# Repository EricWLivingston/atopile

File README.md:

<h1 align="center">
    <picture>
    <source media="(prefers-color-scheme: dark)" srcset="https://github.com/atopile/atopile/assets/9785003/00f19584-18a2-4b5f-9ce4-1248798974dd">
    <source media="(prefers-color-scheme: light)" src="https://github.com/atopile/atopile/assets/9785003/d38941c1-d7c1-42e6-9b94-a62a0996bc19">
    
    </picture>
</h1>

<p align="center">
  <b>EE Agent fork of atopile</b> — an AI electrical-engineering design agent built on top of the atopile compiler.
</p>

<p align="center">
  <a href="https://github.com/atopile/atopile">Upstream atopile</a> ·
  <a href="https://docs.atopile.io/">atopile docs</a> ·
  <a href="LICENSE">MIT License</a>
</p>

---

> **This is a fork.** It tracks [atopile/atopile](https://github.com/atopile/atopile) and adds
> an EE design agent plus the infrastructure it needs (a dual-provider LLM runner, three custom
> design tools, a KiCad schematic emitter, human-readable net naming, and parametric diode
> picking). For the base language, compiler, and toolchain, see the
> [upstream README](https://github.com/atopile/atopile/blob/main/README.md) and
> [docs.atopile.io](https://docs.atopile.io/). Everything below is **what this fork adds.**

## What this fork adds

atopile lets you describe electronics as code (`.ato`) and compiles them to a BOM, netlist, and
KiCad layout. This fork wraps an **agent** around that compiler: it researches a design against an
indexed knowledge base, authors `.ato`, simulates analog subcircuits, drives the build, and emits a
human-readable KiCad schematic — switchable between OpenAI and Anthropic models, with per-turn
model routing for cost control. The agent runs in the existing atopile VS Code extension sidebar.

This is an **early prototype**: the core agent loop, the three tools, and the schematic/net-naming
pipeline are working and tested, but several pieces are stubs or single-vendor (see
[Known limitations](#known-limitations--status)).

## Features

### Dual-provider agent runner — `src/atopile/server/agent/_ee/`
- **`AnthropicProvider`** (`provider_anthropic.py`) implements atopile's `LLMProvider` protocol
  alongside the existing OpenAI provider. It emulates the OpenAI stateful Responses API on top of
  Anthropic's stateless Messages API via an LRU transcript store, and repairs orphaned
  `tool_use`/`tool_result` pairs (the failure class that froze multi-turn runs).
- **Dynamic model routing** (`model_router.py`) — a per-turn complexity classifier routes calls to
  Haiku / Sonnet / Opus tiers, with a content-based floor and mid-turn escalation on repeated build
  failures. Off by default; opt-in, Anthropic-only.
- **Runner safeguards** — per-turn token budget, build-failure detection (the async build queue
  otherwise hides failures from the circuit breaker), and tightened loop/time caps.

### Custom agent tools — `_ee/tools_*.py` + framework-agnostic packages
- **`rag_search`** — retrieval over a datasheet/app-note corpus: `src/ee_agent_rag/`
  (Chroma · LlamaParse-REST · OpenAI embeddings · Cohere rerank, RRF fusion). Tuned to recall@5 ≈
  0.98 on a 50-question eval; thin wrapper degrades to `{ok: false}` on any failure.
- **`pyspice_run`** — simulates an agent-authored SPICE netlist: `src/ee_agent_spice/`
  (PySpice + libngspice, bundled discrete models). Returns per-probe min/max/mean only;
  persists full vectors to disk.
- **`skills_list` / `skill_read`** (`tools_skills.py`) — on-demand skill discovery so the agent
  pulls per-tool guidance just-in-time instead of always-loading it.
- **`ipc_check`** — registered, schema'd graceful **stub** (body TBD).

### KiCad schematic emitter — `src/faebryk/exporters/schematic/`
atopile had no Python `.kicad_sch` writer; this adds one (emitting S-expression text directly,
because `kicad.dumps` mis-writes schematics). Build step `generate_schematic` writes
`<output>.kicad_sch`. Modes (`export_schematic(mode=…)`): **hierarchical** (default — one sheet per
`.ato` module, global labels = a valid netlist), **wired** (provably short-free ladder routing), and
**labels**. Real cached symbols are regenerated into the schematic's native grammar; rails render as
KiCad power symbols. Sheet grouping is refined by connectivity (`schematic.py`:
`_pull_in_by_connectivity`, `_flatten_small_leaves`) so parent-level passives land on the subcircuit
they belong to.

### Human-readable net naming — `src/faebryk/libs/net_naming.py`
Voltage-aware power rails (`+5V` / `+3V3` / `+12V`, from the tightest-spec member), a single shared
`GND` with a fragmentation warning, and an IC-pin fallback for unnamed nets — so the emitted
schematic labels read like a human drew them.

### Parametric diode auto-picking — `src/faebryk/library/Diode.py`, `Pickable.py`
Adds the `DIODES` query endpoint + `is_pickable_by_type` to `Diode`, fixing the silent "ghost
component" drop where an un-pickable diode vanished from the BOM/netlist/PCB while its nets
remained. (MOSFET/LED auto-pick is scoped but deliberately deferred.)

### Agent run-log viewer — `src/ui-server/`, `src/vscode-atopile/`
A new "Agent" mode in the extension's Logs tab streams the agent's own run log
(`agent_events`), so planning, tool calls, and `run_failed` are visible live.

## Configuration

The provider and agent behaviour are env-driven (read once at process start — **restart the backend
/ reload the VS Code window after changing them**):

| Variable | Purpose |
|---|---|
| `EE_AGENT_PROVIDER` | `openai` (default, upstream behaviour) or `anthropic` |
| `ATOPILE_AGENT_ANTHROPIC_API_KEY` / `ANTHROPIC_API_KEY` | Anthropic credentials |
| `EE_AGENT_DYNAMIC_MODEL` | `1` enables per-turn model routing (Anthropic only; off by default) |
| `ATOPILE_AGENT_MODEL_COMPLEX` | complex-tier model (default Sonnet; set to `claude-opus-4-8` to opt into Opus) |
| `ATOPILE_AGENT_MAX_TURN_TOKENS` / `ATOPILE_AGENT_MAX_BUILD_FAILURES` | per-turn spend / failure budgets |
| `OPENAI_API_KEY` / `LLAMA_CLOUD_API_KEY` / `COHERE_API_KEY` | `rag_search` ingest + query (see `.env.example`) |
| `EE_DATA_ROOT` | RAG corpus/index root (defaults to the source tree) |
| `EE_SPICE_NGSPICE_LIB` / `EE_SPICE_TIMEOUT_S` | libngspice path override / sim wall-clock timeout |

`rag_search` needs a `brew`/pip RAG stack; `pyspice_run` needs `brew install ngspice` (libngspice 46).

## Testing

Run the suite with `ato dev test` (or `pytest -q`). The fork adds **18 test files / ~195 tests**:

- `test/server/agent/` — Anthropic provider, model router, runner safeguards, tool plumbing
- `test/exporters/` — schematic emitter + connectivity placement
- `test/ee_agent_rag/` — RAG pipeline + table-fidelity
- `test/ee_agent_spice/` — SPICE runner (+ a live, auto-skipped tier)

## Known limitations & status

- **`ipc_check` is a stub** — registered and model-callable, but returns a placeholder; it depends on
  a standards corpus (IPC-2221/2152) not yet ingested.
- **Single-vendor auto-pick** — only diodes auto-pick; MOSFETs/LEDs/other actives remain manual.
- **Silent-ghost UX** — an un-pickable, un-footprinted module still logs only `ATTENTION: …` and the
  build reports success (`src/faebryk/libs/picker/picker.py:165`); diodes are fixed, other types are
  not. Promoting that to a visible warning is a one-line policy change with upstream-visible impact.
- **Schematic real-symbol lookup** misses parts whose cached directory name doesn't match the
  sanitized manufacturer string — they fall back to a (electrically complete) generic box.
- **Dynamic routing is Anthropic-only and per-turn** — because the agent runs a whole design as one
  turn, the per-turn route effectively pins the whole run; the OpenAI path is unverified for mid-chain
  model switches, so routing is forced off there. The per-turn token budget does **not** count cache
  reads.
- **RAG corpus is datasheets + app-notes only** — standards/textbook chunkers are pending.
- **`kicad.dumps` for schematics is broken upstream** — worked around by emitting S-expression text;
  a clean upstream fix is a contribution candidate.

## License

MIT — same as upstream atopile. See `LICENSE`.

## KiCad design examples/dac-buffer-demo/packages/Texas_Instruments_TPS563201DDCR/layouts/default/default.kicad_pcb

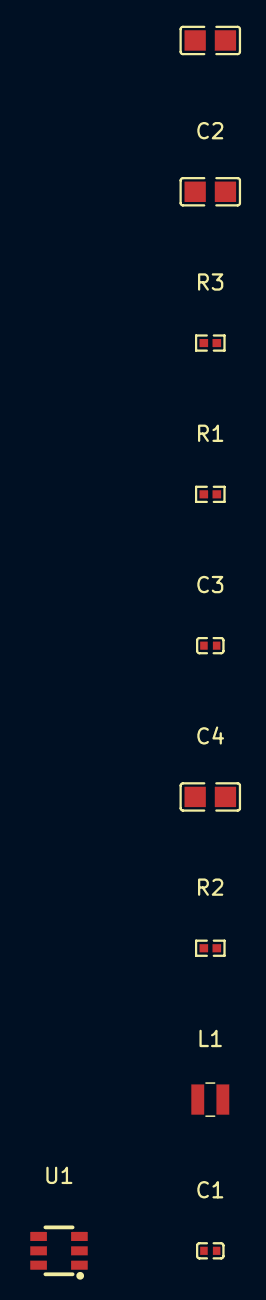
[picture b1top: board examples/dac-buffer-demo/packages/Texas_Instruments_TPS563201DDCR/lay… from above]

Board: 2 copper layers, 10 parts (0 on the bottom side), 7 nets, no tracks yet.

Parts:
C1, C3: 100nF; C0402
C2: 10µF; C0805
C4, C5: 22µF; C0805
L1: L 4.7µH; IND-SMD_L2.5-W2.0-VLS252012CX-150M
R1: 100kΩ; R0402
R2: 10kΩ; R0402
R3: 54.9kΩ; R0402
U1: SOT-23-6_L2.9-W1.6-P0.95-LS2.8-BR

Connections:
EN: R1.1, U1.5
VFB: R2.1, R3.2, U1.4
cin_hf-power-hv: C2.1, C3.1, R1.2, U1.3
cout[1]-power-hv: C4.1, C5.1, L1.2, R3.1
cout[1]-power-lv: C2.2, C3.2, C4.2, C5.2, R2.2, U1.1
hv: C1.1, U1.6
lv: C1.2, L1.1, U1.2

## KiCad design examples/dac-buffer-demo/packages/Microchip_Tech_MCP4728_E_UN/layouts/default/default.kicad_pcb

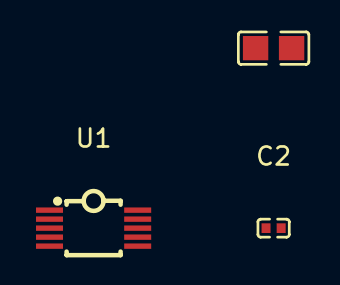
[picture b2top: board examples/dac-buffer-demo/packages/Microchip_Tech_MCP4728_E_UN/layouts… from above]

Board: 2 copper layers, 3 parts (0 on the bottom side), 2 nets, no tracks yet.

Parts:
C1: 10µF; C0805
C2: 100nF; C0402
U1: MSOP-10_L3.0-W3.0-P0.50-LS5.0-TL

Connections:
hv: C1.1, C2.1, U1.1
lv: C1.2, C2.2, U1.10

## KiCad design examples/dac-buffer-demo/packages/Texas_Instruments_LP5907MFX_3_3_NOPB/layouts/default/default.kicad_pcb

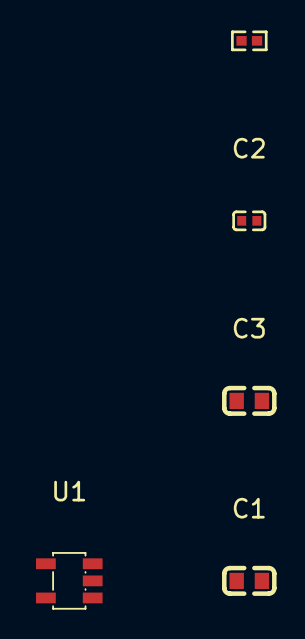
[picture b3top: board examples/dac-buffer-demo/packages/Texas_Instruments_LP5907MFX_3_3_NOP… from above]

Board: 2 copper layers, 5 parts (0 on the bottom side), 4 nets, no tracks yet.

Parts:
C1, C3: 1µF; C0603
C2: 10nF; C0402
R1: 100kΩ; R0402
U1: SOT-23-5_L3.0-W1.7-P0.95-LS2.8-BR

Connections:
cnr-power-hv: C2.1, R1.1, U1.3
cout-power-hv: C3.1, U1.5
hv: C1.1, R1.2, U1.1
lv: C1.2, C2.2, C3.2, U1.2

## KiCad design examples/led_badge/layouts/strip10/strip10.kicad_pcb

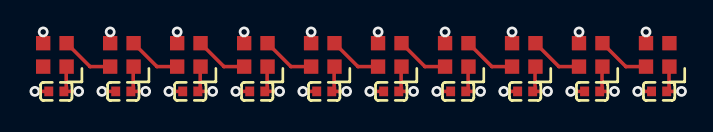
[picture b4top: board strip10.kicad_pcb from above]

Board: 2 copper layers, 20 parts (0 on the bottom side), 11 nets.

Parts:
C1, C2, C3, C4, C5, C6, C7, C8, C9, C10: 100nF; C0402
LED1, LED2, LED3, LED4, LED5, LED6, LED7, LED8, LED9, LED10: LED-SMD_4P-L2.0-W2.0-BR

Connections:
hv: C1.1, C2.1, C3.1, C4.1, C5.1, C6.1, C7.1, C8.1, C9.1, C10.1, LED1.1, LED2.1, LED3.1, LED4.1, LED5.1, LED6.1, LED7.1, LED8.1, LED9.1, LED10.1
leds[1]-data_in-DIN: LED1.2, LED2.4
leds[2]-data_in-DIN: LED2.2, LED3.4
leds[3]-data_in-DIN: LED3.2, LED4.4
leds[4]-data_in-DIN: LED4.2, LED5.4
leds[5]-data_in-DIN: LED5.2, LED6.4
leds[6]-data_in-DIN: LED6.2, LED7.4
leds[7]-data_in-DIN: LED7.2, LED8.4
leds[8]-data_in-DIN: LED8.2, LED9.4
leds[9]-data_in-DIN: LED9.2, LED10.4
lv: C1.2, C2.2, C3.2, C4.2, C5.2, C6.2, C7.2, C8.2, C9.2, C10.2, LED1.3, LED2.3, LED3.3, LED4.3, LED5.3, LED6.3, LED7.3, LED8.3, LED9.3, LED10.3

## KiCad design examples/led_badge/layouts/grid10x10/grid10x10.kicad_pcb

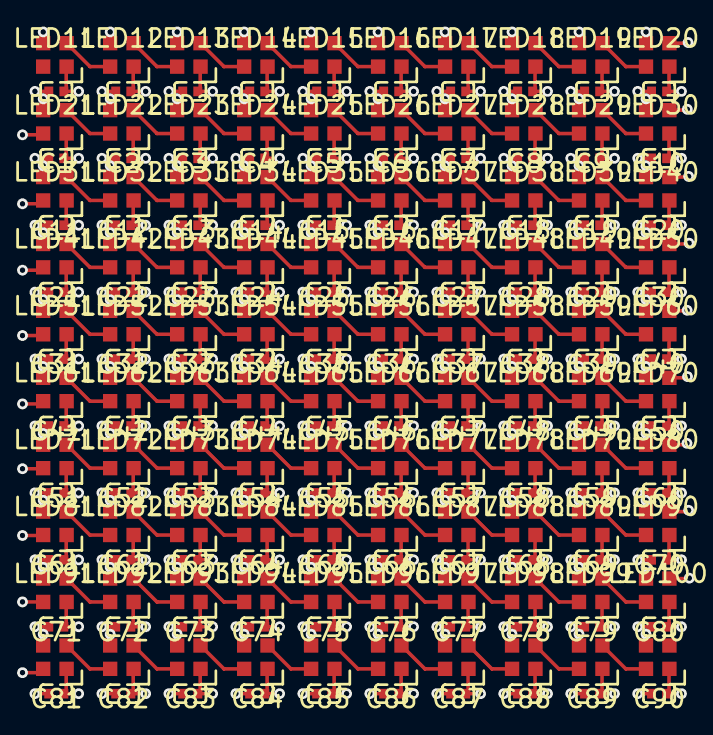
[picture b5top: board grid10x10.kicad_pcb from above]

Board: 4 copper layers, 200 parts (0 on the bottom side), 101 nets.

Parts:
C1, C2, C3, C4, C5, C6, C7, C8, C9, C10, C11, C12, C13, C14, C15, C16, C17, C18, C19, C20, C21, C22, C23, C24, C25, C26, C27, C28, C29, C30, C31, C32, C33, C34, C35, C36, C37, C38, C39, C40, C41, C42, C43, C44, C45, C46, C47, C48, C49, C50, C51, C52, C53, C54, C55, C56, C57, C58, C59, C60, C61, C62, C63, C64, C65, C66, C67, C68, C69, C70, C71, C72, C73, C74, C75, C76, C77, C78, C79, C80, C81, C82, C83, C84, C85, C86, C87, C88, C89, C90, C91, C92, C93, C94, C95, C96, C97, C98, C99, C100: 100nF; C0402
LED1, LED2, LED3, LED4, LED5, LED6, LED7, LED8, LED9, LED10, LED11, LED12, LED13, LED14, LED15, LED16, LED17, LED18, LED19, LED20, LED21, LED22, LED23, LED24, LED25, LED26, LED27, LED28, LED29, LED30, LED31, LED32, LED33, LED34, LED35, LED36, LED37, LED38, LED39, LED40, LED41, LED42, LED43, LED44, LED45, LED46, LED47, LED48, LED49, LED50, LED51, LED52, LED53, LED54, LED55, LED56, LED57, LED58, LED59, LED60, LED61, LED62, LED63, LED64, LED65, LED66, LED67, LED68, LED69, LED70, LED71, LED72, LED73, LED74, LED75, LED76, LED77, LED78, LED79, LED80, LED81, LED82, LED83, LED84, LED85, LED86, LED87, LED88, LED89, LED90, LED91, LED92, LED93, LED94, LED95, LED96, LED97, LED98, LED99, LED100: LED-SMD_4P-L2.0-W2.0-BR

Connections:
DIN: LED1.2, LED2.4
hv: C1.1, C2.1, C3.1, C4.1, C5.1, C6.1, C7.1, C8.1, C9.1, C10.1, C11.1, C12.1, C13.1, C14.1, C15.1, C16.1, C17.1, C18.1, C19.1, C20.1, C21.1, C22.1, C23.1, C24.1, C25.1, C26.1, C27.1, C28.1, C29.1, C30.1, C31.1, C32.1, C33.1, C34.1, C35.1, C36.1, C37.1, C38.1, C39.1, C40.1, C41.1, C42.1, C43.1, C44.1, C45.1, C46.1, C47.1, C48.1, C49.1, C50.1, C51.1, C52.1, C53.1, C54.1, C55.1, C56.1, C57.1, C58.1, C59.1, C60.1, C61.1, C62.1, C63.1, C64.1, C65.1, C66.1, C67.1, C68.1, C69.1, C70.1, C71.1, C72.1, C73.1, C74.1, C75.1, C76.1, C77.1, C78.1, C79.1, C80.1, C81.1, C82.1, C83.1, C84.1, C85.1, C86.1, C87.1, C88.1, C89.1, C90.1, C91.1, C92.1, C93.1, C94.1, C95.1, C96.1, C97.1, C98.1, C99.1, C100.1, LED1.1, LED2.1, LED3.1, LED4.1, LED5.1, LED6.1, LED7.1, LED8.1, LED9.1, LED10.1, LED11.1, LED12.1, LED13.1, LED14.1, LED15.1, LED16.1, LED17.1, LED18.1, LED19.1, LED20.1, LED21.1, LED22.1, LED23.1, LED24.1, LED25.1, LED26.1, LED27.1, LED28.1, LED29.1, LED30.1, LED31.1, LED32.1, LED33.1, LED34.1, LED35.1, LED36.1, LED37.1, LED38.1, LED39.1, LED40.1, LED41.1, LED42.1, LED43.1, LED44.1, LED45.1, LED46.1, LED47.1, LED48.1, LED49.1, LED50.1, LED51.1, LED52.1, LED53.1, LED54.1, LED55.1, LED56.1, LED57.1, LED58.1, LED59.1, LED60.1, LED61.1, LED62.1, LED63.1, LED64.1, LED65.1, LED66.1, LED67.1, LED68.1, LED69.1, LED70.1, LED71.1, LED72.1, LED73.1, LED74.1, LED75.1, LED76.1, LED77.1, LED78.1, LED79.1, LED80.1, LED81.1, LED82.1, LED83.1, LED84.1, LED85.1, LED86.1, LED87.1, LED88.1, LED89.1, LED90.1, LED91.1, LED92.1, LED93.1, LED94.1, LED95.1, LED96.1, LED97.1, LED98.1, LED99.1, LED100.1
leds[1]-data_in-DIN: LED11.2, LED12.4
leds[1]-data_in-DIN-1: LED21.2, LED22.4
leds[1]-data_in-DIN-2: LED31.2, LED32.4
leds[1]-data_in-DIN-3: LED41.2, LED42.4
leds[1]-data_in-DIN-4: LED51.2, LED52.4
leds[1]-data_in-DIN-5: LED61.2, LED62.4
leds[1]-data_in-DIN-6: LED71.2, LED72.4
leds[1]-data_in-DIN-7: LED81.2, LED82.4
leds[1]-data_in-DIN-8: LED91.2, LED92.4
leds[2]-data_in-DIN: LED2.2, LED3.4
leds[2]-data_in-DIN-1: LED12.2, LED13.4
leds[2]-data_in-DIN-2: LED22.2, LED23.4
leds[2]-data_in-DIN-3: LED32.2, LED33.4
leds[2]-data_in-DIN-4: LED42.2, LED43.4
leds[2]-data_in-DIN-5: LED52.2, LED53.4
leds[2]-data_in-DIN-6: LED62.2, LED63.4
leds[2]-data_in-DIN-7: LED72.2, LED73.4
leds[2]-data_in-DIN-8: LED82.2, LED83.4
leds[2]-data_in-DIN-9: LED92.2, LED93.4
leds[3]-data_in-DIN: LED3.2, LED4.4
leds[3]-data_in-DIN-1: LED13.2, LED14.4
leds[3]-data_in-DIN-2: LED23.2, LED24.4
leds[3]-data_in-DIN-3: LED33.2, LED34.4
leds[3]-data_in-DIN-4: LED43.2, LED44.4
leds[3]-data_in-DIN-5: LED53.2, LED54.4
leds[3]-data_in-DIN-6: LED63.2, LED64.4
leds[3]-data_in-DIN-7: LED73.2, LED74.4
leds[3]-data_in-DIN-8: LED83.2, LED84.4
leds[3]-data_in-DIN-9: LED93.2, LED94.4
leds[4]-data_in-DIN: LED4.2, LED5.4
leds[4]-data_in-DIN-1: LED14.2, LED15.4
leds[4]-data_in-DIN-2: LED24.2, LED25.4
leds[4]-data_in-DIN-3: LED34.2, LED35.4
leds[4]-data_in-DIN-4: LED44.2, LED45.4
leds[4]-data_in-DIN-5: LED54.2, LED55.4
leds[4]-data_in-DIN-6: LED64.2, LED65.4
leds[4]-data_in-DIN-7: LED74.2, LED75.4
leds[4]-data_in-DIN-8: LED84.2, LED85.4
leds[4]-data_in-DIN-9: LED94.2, LED95.4
leds[5]-data_in-DIN: LED5.2, LED6.4
leds[5]-data_in-DIN-1: LED15.2, LED16.4
leds[5]-data_in-DIN-2: LED25.2, LED26.4
leds[5]-data_in-DIN-3: LED35.2, LED36.4
leds[5]-data_in-DIN-4: LED45.2, LED46.4
leds[5]-data_in-DIN-5: LED55.2, LED56.4
leds[5]-data_in-DIN-6: LED65.2, LED66.4
leds[5]-data_in-DIN-7: LED75.2, LED76.4
leds[5]-data_in-DIN-8: LED85.2, LED86.4
leds[5]-data_in-DIN-9: LED95.2, LED96.4
leds[6]-data_in-DIN: LED6.2, LED7.4
leds[6]-data_in-DIN-1: LED16.2, LED17.4
leds[6]-data_in-DIN-2: LED26.2, LED27.4
leds[6]-data_in-DIN-3: LED36.2, LED37.4
leds[6]-data_in-DIN-4: LED46.2, LED47.4
leds[6]-data_in-DIN-5: LED56.2, LED57.4
leds[6]-data_in-DIN-6: LED66.2, LED67.4
leds[6]-data_in-DIN-7: LED76.2, LED77.4
leds[6]-data_in-DIN-8: LED86.2, LED87.4
leds[6]-data_in-DIN-9: LED96.2, LED97.4
leds[7]-data_in-DIN: LED7.2, LED8.4
leds[7]-data_in-DIN-1: LED17.2, LED18.4
leds[7]-data_in-DIN-2: LED27.2, LED28.4
leds[7]-data_in-DIN-3: LED37.2, LED38.4
leds[7]-data_in-DIN-4: LED47.2, LED48.4
leds[7]-data_in-DIN-5: LED57.2, LED58.4
leds[7]-data_in-DIN-6: LED67.2, LED68.4
leds[7]-data_in-DIN-7: LED77.2, LED78.4
leds[7]-data_in-DIN-8: LED87.2, LED88.4
leds[7]-data_in-DIN-9: LED97.2, LED98.4
leds[8]-data_in-DIN: LED8.2, LED9.4
leds[8]-data_in-DIN-1: LED18.2, LED19.4
leds[8]-data_in-DIN-2: LED28.2, LED29.4
leds[8]-data_in-DIN-3: LED38.2, LED39.4
leds[8]-data_in-DIN-4: LED48.2, LED49.4
leds[8]-data_in-DIN-5: LED58.2, LED59.4
leds[8]-data_in-DIN-6: LED68.2, LED69.4
leds[8]-data_in-DIN-7: LED78.2, LED79.4
leds[8]-data_in-DIN-8: LED88.2, LED89.4
leds[8]-data_in-DIN-9: LED98.2, LED99.4
leds[9]-data_in-DIN: LED9.2, LED10.4
leds[9]-data_in-DIN-1: LED19.2, LED20.4
leds[9]-data_in-DIN-2: LED29.2, LED30.4
leds[9]-data_in-DIN-3: LED39.2, LED40.4
leds[9]-data_in-DIN-4: LED49.2, LED50.4
leds[9]-data_in-DIN-5: LED59.2, LED60.4
leds[9]-data_in-DIN-6: LED69.2, LED70.4
leds[9]-data_in-DIN-7: LED79.2, LED80.4
leds[9]-data_in-DIN-8: LED89.2, LED90.4
leds[9]-data_in-DIN-9: LED99.2, LED100.4
lv: C1.2, C2.2, C3.2, C4.2, C5.2, C6.2, C7.2, C8.2, C9.2, C10.2, C11.2, C12.2, C13.2, C14.2, C15.2, C16.2, C17.2, C18.2, C19.2, C20.2, C21.2, C22.2, C23.2, C24.2, C25.2, C26.2, C27.2, C28.2, C29.2, C30.2, C31.2, C32.2, C33.2, C34.2, C35.2, C36.2, C37.2, C38.2, C39.2, C40.2, C41.2, C42.2, C43.2, C44.2, C45.2, C46.2, C47.2, C48.2, C49.2, C50.2, C51.2, C52.2, C53.2, C54.2, C55.2, C56.2, C57.2, C58.2, C59.2, C60.2, C61.2, C62.2, C63.2, C64.2, C65.2, C66.2, C67.2, C68.2, C69.2, C70.2, C71.2, C72.2, C73.2, C74.2, C75.2, C76.2, C77.2, C78.2, C79.2, C80.2, C81.2, C82.2, C83.2, C84.2, C85.2, C86.2, C87.2, C88.2, C89.2, C90.2, C91.2, C92.2, C93.2, C94.2, C95.2, C96.2, C97.2, C98.2, C99.2, C100.2, LED1.3, LED2.3, LED3.3, LED4.3, LED5.3, LED6.3, LED7.3, LED8.3, LED9.3, LED10.3, LED11.3, LED12.3, LED13.3, LED14.3, LED15.3, LED16.3, LED17.3, LED18.3, LED19.3, LED20.3, LED21.3, LED22.3, LED23.3, LED24.3, LED25.3, LED26.3, LED27.3, LED28.3, LED29.3, LED30.3, LED31.3, LED32.3, LED33.3, LED34.3, LED35.3, LED36.3, LED37.3, LED38.3, LED39.3, LED40.3, LED41.3, LED42.3, LED43.3, LED44.3, LED45.3, LED46.3, LED47.3, LED48.3, LED49.3, LED50.3, LED51.3, LED52.3, LED53.3, LED54.3, LED55.3, LED56.3, LED57.3, LED58.3, LED59.3, LED60.3, LED61.3, LED62.3, LED63.3, LED64.3, LED65.3, LED66.3, LED67.3, LED68.3, LED69.3, LED70.3, LED71.3, LED72.3, LED73.3, LED74.3, LED75.3, LED76.3, LED77.3, LED78.3, LED79.3, LED80.3, LED81.3, LED82.3, LED83.3, LED84.3, LED85.3, LED86.3, LED87.3, LED88.3, LED89.3, LED90.3, LED91.3, LED92.3, LED93.3, LED94.3, LED95.3, LED96.3, LED97.3, LED98.3, LED99.3, LED100.3
rows[1]-data_in-line: LED10.2, LED11.4
rows[2]-data_in-line: LED20.2, LED21.4
rows[3]-data_in-line: LED30.2, LED31.4
rows[4]-data_in-line: LED40.2, LED41.4
rows[5]-data_in-line: LED50.2, LED51.4
rows[6]-data_in-line: LED60.2, LED61.4
rows[7]-data_in-line: LED70.2, LED71.4
rows[8]-data_in-line: LED80.2, LED81.4
rows[9]-data_in-line: LED90.2, LED91.4
